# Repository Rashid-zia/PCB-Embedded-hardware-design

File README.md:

# 3W Audio Amplifier – PCB Design and Layout (EAGLE)

## 📌 Project Overview
This project focuses on the design and PCB layout of a 3W audio amplifier, developed as part of my bachelor studies in Applied Informatics in Industrial Automation. The goal was to design a compact, manufacturable, and reliable double-sided PCB, including schematic design, component selection, custom footprint creation, and layout optimization using Autodesk EAGLE.

This project strengthened my practical understanding of analog electronics, PCB design principles, and hardware implementation workflows, which are essential skills in robotics and embedded systems engineering.

---

## Objectives
- Design a functional 3W audio amplifier circuit
- Create schematic and PCB layout using EAGLE
- Design custom component footprints
- Optimize routing, grounding, and power distribution
- Ensure manufacturability and compliance with PCB layout standards
- Prepare fabrication-ready design files

---

## Tools & Technologies
- EDA Software: Autodesk EAGLE  
- PCB Type:** Double-sided PCB  
- Design Tasks:
  - Schematic capture  
  - Component selection  
  - Custom footprint creation  
  - PCB layout & routing  
  - Design rule checks (DRC)  
  - Manufacturing file generation  

---

## Key Features
- Compact double-layer PCB design  
- Optimized signal routing and grounding  
- Proper power trace sizing  
- Noise-minimized analog layout  
- Manufacturing-ready design  

-----

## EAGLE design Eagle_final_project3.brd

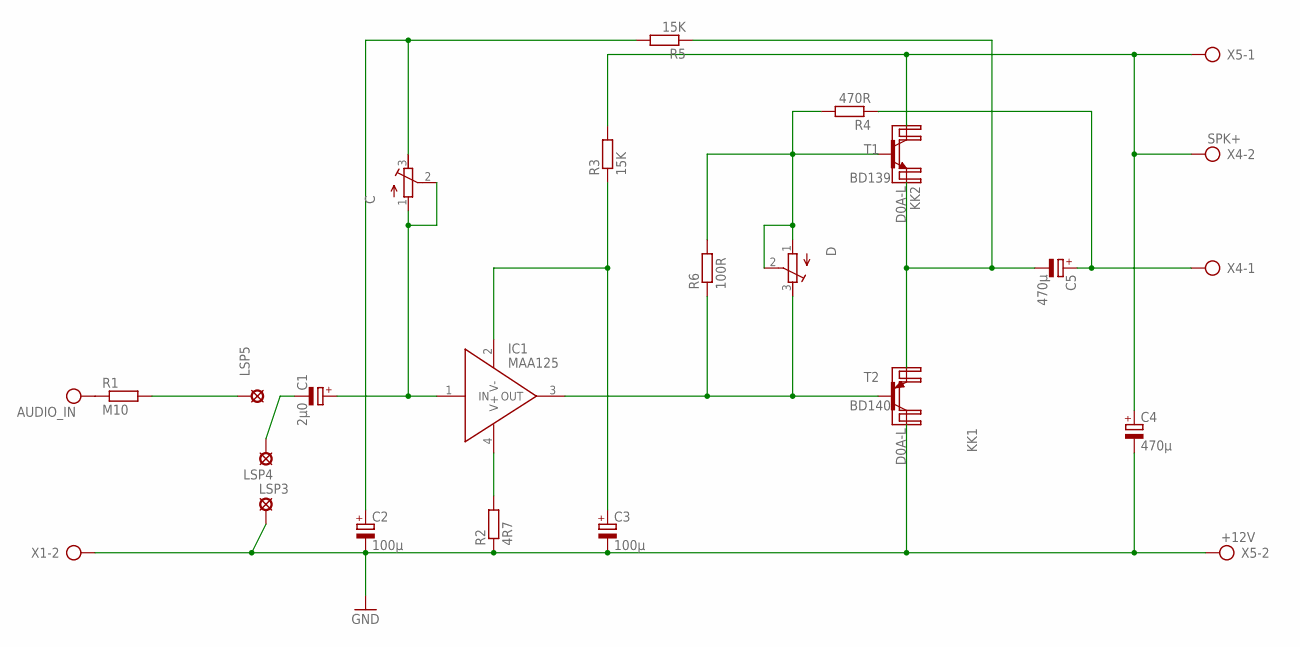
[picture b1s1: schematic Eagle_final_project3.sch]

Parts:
C: R-TRIMM3339P; RTRIM3339P
C1: 2µ0; E2-5
C2, C3: 100µ; E2-5
C4: 470µ; E2-5
C5: 470µ; E2,5-6
D: R-TRIMM3339P; RTRIM3339P
IC1: MAA125; IO-1
KK1, KK2: D0A-L; D02A-L
LSP3, LSP4, LSP5: LSP10
Q1: BD139; TO126
R1: M10; 0207/10
R2: 4R7; 0207/10
R3, R5: 15K; 0207/10
R4: 470R; 0207/10
R6: 100R; 0207/10
T2: BD140; TO126
X1: AUDIO_IN; AK300/2
X4: SPK+; AK300/2
X5: +12V; AK300/2

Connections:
GND: C2.-, C3.-, C4.-, LSP3.MP, R2.1, T2.2 (C), X1.2, X5.2
unnamed: LSP5.MP, R1.2
unnamed: C.1 (A), C.2 (S), C1.+, IC1.1 (IN)
unnamed: D.3 (E), IC1.3 (OUT), R6.1, T2.3 (B)
unnamed: IC1.4 (V+), R2.2
unnamed: C3.+, IC1.2 (V-), R3.1
unnamed: C.3 (E), C2.+, R5.2
unnamed: C5.+, R4.1, X4.1
unnamed: C4.+, Q1.2 (C), R3.2, X4.2, X5.1
unnamed: C5.-, Q1.1 (E), R5.1, T2.1 (E)
unnamed: C1.-, LSP4.MP
unnamed: R1.1, X1.1
T1: D.1 (A), D.2 (S), Q1.3 (B), R4.2, R6.2

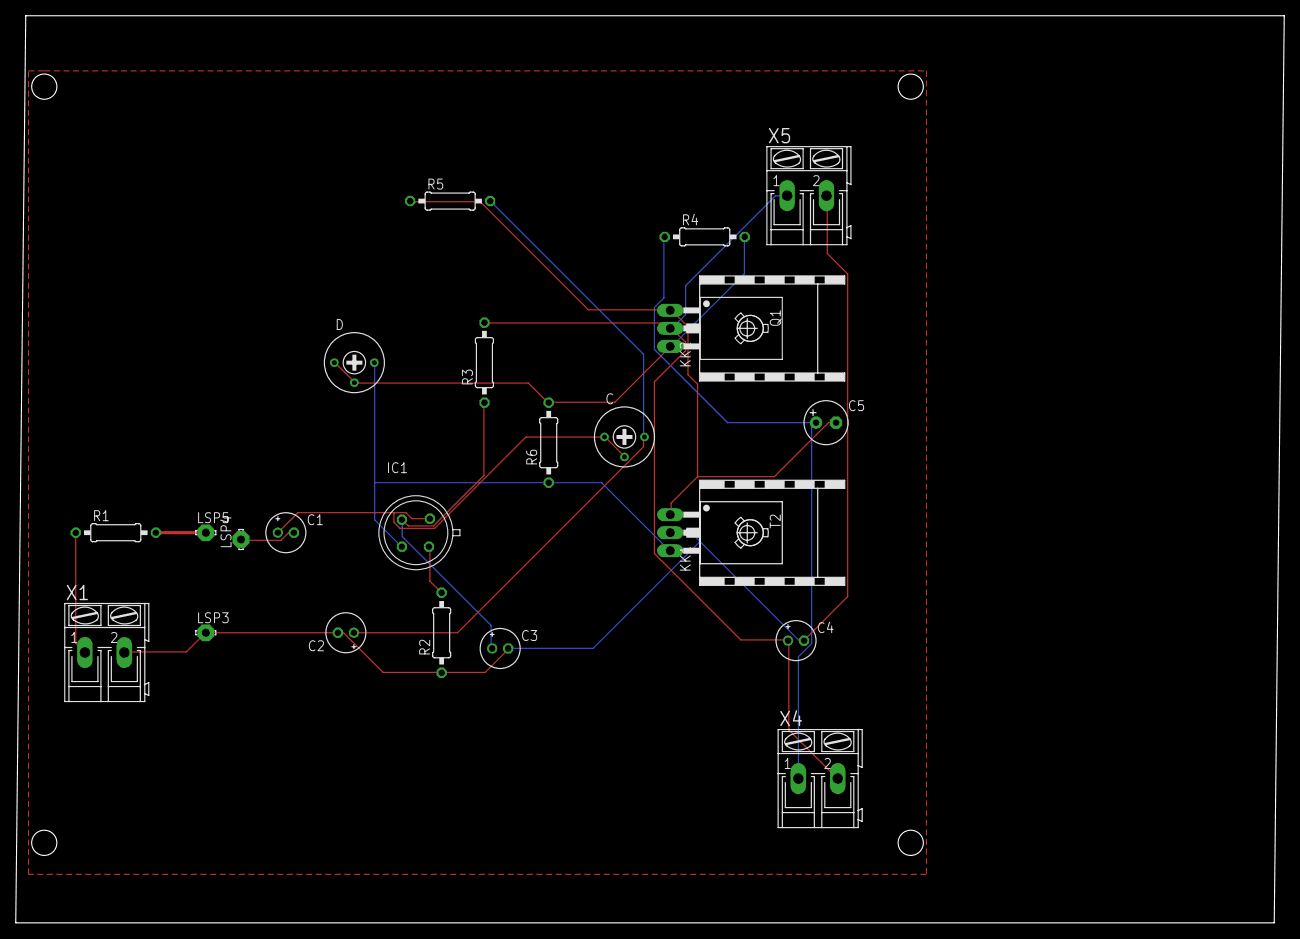
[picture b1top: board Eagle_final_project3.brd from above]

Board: 2 copper layers, 161.0 x 115.2 mm, 24 parts (0 on the bottom side), 13 nets.

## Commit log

2026-02-28 Add README for 3W Audio Amplifier PCB project
    Added project overview, objectives, tools, and key features for the 3W audio amplifier PCB design.
